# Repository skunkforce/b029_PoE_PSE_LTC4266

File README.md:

# edgy_board number b029
This design is part of the [edgy board project](https://github.com/skunkforce/edgy_boards). It provides PoE PSE functionality configurable beyond 100W.

# getting started
This repository uses submodules. After cloning use the command 

```$ git submodule update --init --recursive```

to pull the submodules before opening the project with kicad. 

# Tests
Tests can be found in [TESTS.md](TESTS.md)

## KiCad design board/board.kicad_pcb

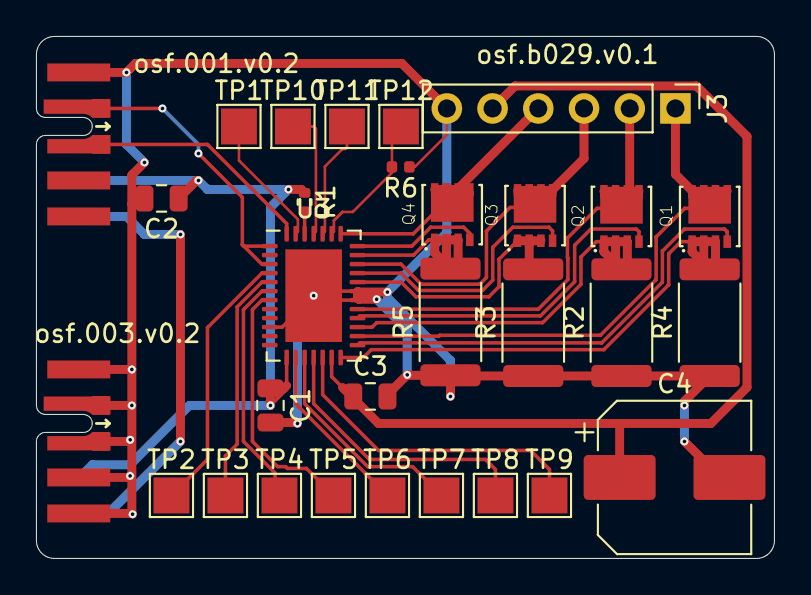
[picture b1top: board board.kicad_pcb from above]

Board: 2 copper layers, 41.0 x 29.0 mm, 30 parts (0 on the bottom side), 31 nets.

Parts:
C1: 100nF; C_0805_2012Metric
C2, C3: 1uF; C_0805_2012Metric
C4: 100uF; CP_Elec_8x5.4
J1: 001_I2C; on_edge_2x05_device
J2: 003_power; on_edge_2x05_device
J3: Conn_01x06_Male; PinHeader_1x06_P2.54mm_Vertical
Q1, Q2, Q3, Q4: FDMC86102LZ; TRANS_FDMC86102LZ
R1: 2.2k; R_0402_1005Metric
R2, R3, R4, R5: 250m; R_2512_6332Metric
R6: 0R; R_0402_1005Metric
TP1: int_tp; TestPoint_Pad_2.0x2.0mm
TP2, TP3, TP4, TP5, TP6, TP7, TP8, TP9, TP10, TP11, TP12: tp; TestPoint_Pad_2.0x2.0mm
U3: LTC4266AIUHF-4#PBF; QFN-38-1EP_5x7mm_P0.5mm_EP3.15x5.15mm

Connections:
+3V3: C1.1, C2.1, J1.9, J2.9, R1.1, U3.13
/Controller/SCL: J1.3, U3.38
/Controller/SDA: J1.2, U3.1, U3.3
/Controller/SW1: J3.4, Q4.2, U3.32
/Controller/SW2: J3.3, Q3.2, U3.29
/Controller/SW3: J3.2, Q2.2, U3.24
/Controller/SW4: J3.1, Q1.2, U3.21
/Controller/int: TP1.1, U3.37
/Controller/poe+: C3.1, C4.1, J3.5, U3.18
GND: C1.2, C2.2, C3.2, C4.2, J1.1, J2.1, J2.2, J2.3, J2.4, J2.5, J3.6, R2.1, R3.1, R4.1, R5.1, R6.1, U3.10, U3.25, U3.26, U3.39
unnamed: J1.10, J2.10
unnamed: Q1.1, U3.20
unnamed: Q1.3, R4.2, U3.19
unnamed: Q2.1, U3.23
unnamed: Q2.3, R2.2, U3.22
unnamed: Q3.1, U3.28
unnamed: Q3.3, R3.2, U3.27
unnamed: Q4.1, U3.31
unnamed: Q4.3, R5.2, U3.30
unnamed: R1.2, U3.36
unnamed: R6.2, TP12.1, U3.33
unnamed: TP2.1, U3.4
unnamed: TP3.1, U3.5
unnamed: TP4.1, U3.6
unnamed: TP5.1, U3.7
unnamed: TP6.1, U3.14
unnamed: TP7.1, U3.15
unnamed: TP8.1, U3.16
unnamed: TP9.1, U3.17
unnamed: TP10.1, U3.35
unnamed: TP11.1, U3.34

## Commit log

2023-02-24 improved description
2023-02-24 imported legacy version
